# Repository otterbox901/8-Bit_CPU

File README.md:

# 8-Bit CPU

A microcoded 8-bit CPU built from 24 74HC-series logic and memory ICs: custom
instruction set, 4 general-purpose registers, add/subtract ALU with Zero and
Carry flags, and a control unit driven entirely by two EEPROMs.

*Preview from JLCPCB

## Status: In progress

- [x] Instruction set (10 instructions, 1- and 2-byte encodings)
- [x] Microcode ROM generator (`ROM/microcode_rom_gen.py`)
- [x] Emulator + assembler, full test program passing
- [x] Schematic: 24 ICs, 0 ERC errors
- [x] Schematic verified by simulation: the KiCad netlist runs the test program
      at the chip-pin level with the real ROM images (`kicad_files/sim_netlist.py`)
- [x] PCB: 2-layer, 160 × 140 mm, fully routed (Freerouting), GND pour on
      both layers; DRC clean (0 errors, 0 warnings, 0 unconnected) and 0
      schematic-parity differences
- [x] Fabrication outputs: Gerbers + drill (`fab/8-bit-cpu-gerbers.zip`),
      BOM and pick-and-place files
- [ ] Order boards, burn the EEPROMs, and bring up the hardware

## Overview

| | |
|---|---|
| Data path | 8-bit |
| Registers | R0–R3 (2 × 74HC670 register file), plus PC, MAR, IR, A, TEMP |
| Control unit | Microcoded: 2 × 28C256, addressed by opcode, 2-bit step, Z, C |
| ALU | Add, subtract (two's complement), Zero and Carry flags |
| Memory | Harvard: 256 B program EEPROM (28C64), 256 B data SRAM (6116) |
| Clock | 1 MHz canned oscillator (target 1–2 MHz), or external via jumper |
| IC count | 24 (+ oscillator) |
| Board | 2-layer, 160 × 140 mm, SMD logic; EEPROMs and SRAM in DIP sockets so they can be reprogrammed |
| Power | USB-C, 5 V, polyfuse |

## Instruction Set

| Opcode | Mnemonic | Bytes | Operation |
|---|---|---|---|
| `0000` | `NOP` | 1 | No operation |
| `0001` | `LOAD Rd, addr` | 2 | Rd ← RAM[addr] |
| `0010` | `STORE Rd, addr` | 2 | RAM[addr] ← Rd |
| `0011` | `ADD Rd, Rs` | 1 | Rd ← Rd + Rs (sets Z, C) |
| `0100` | `SUB Rd, Rs` | 1 | Rd ← Rd − Rs (sets Z, C; C=1 means no borrow) |
| `0101` | `JMP addr` | 2 | PC ← addr |
| `0110` | `JZ addr` | 2 | PC ← addr if Z |
| `0111` | `JC addr` | 2 | PC ← addr if C |
| `1000` | `MOV Rd, Rs` | 1 | Rd ← Rs |
| `1111` | `HLT` | 1 | Stop the clock |

Unused opcodes behave as `NOP`. Encoding: byte 0 is `[opcode:4][Rd:2][Rs:2]`;
address instructions add one address byte.

Every instruction takes 4 clock cycles (the 2-bit step counter wraps). Step 0
is always the fetch; conditional jumps are resolved by the control ROM, since
Z and C are part of its address.

## Control ROM

`ROM/microcode_rom_gen.py` walks all 256 `(opcode, step, Z, C)` addresses
and writes `microcode_table.csv` (human-readable) and `rom1.bin` / `rom2.bin`
(32 KB images for the two 28C256s). Active-low signals are stored inverted,
so the ROM outputs drive chip enable pins directly without inverter chips.

```bash
cd ROM && python3 microcode_rom_gen.py
```

## Emulator

`emulator.py` runs programs against `microcode_table.csv` directly, and
includes a two-pass assembler (labels, hex/decimal, `.byte`, `.ram addr, val`).

```bash
python3 emulator.py test_program.asm           # full ISA test, 6/6 checks
python3 emulator.py test_program.asm --trace-micro
python3 emulator.py -q test_program.asm        # results only
```

## Schematic

`kicad_files/8-bit cpu.kicad_sch` is **generated**: edit the `PARTS` tables in
`gen_schematic.py` and re-run it. It uses only KiCad's stock symbol and
footprint libraries, except for the 6116 symbol, which is embedded.

```bash
cd kicad_files
python3 gen_schematic.py     # rewrite the schematic
python3 sim_netlist.py       # run test_program.asm on the netlist itself
```

`sim_netlist.py` exports the netlist with `kicad-cli` and models every chip by
its datasheet pin numbers. It fails on bus contention, floating inputs, or
wrong results. Swapped bus bits and a stuck output enable were both confirmed
to be caught.

## PCB

### Ordering the board

Upload `fab/8-bit-cpu-gerbers.zip` to JLCPCB, PCBWay, etc. with:

| Setting | Value |
|---|---|
| Layers | 2 |
| Size | 160 × 140 mm |
| Thickness | 1.6 mm |
| Copper | 1 oz |
| Min track / space | 0.187 mm / 0.2 mm (standard service) |
| Min hole | 0.3 mm (vias 0.6 / 0.3 mm) |
| Plated slots | Yes: 4 on the USB-C shell (0.6 × 1.2 mm) |
| Surface finish | Any (HASL is fine) |

Checked before export: DRC with freshly refilled zones reports 0 errors, 0
warnings, 0 unconnected and 0 schematic-parity issues. The drill file holds
exactly the board's 454 plated holes (329 vias + 125 pads) plus 4 NPTH
mounting holes.

`fab/bom.csv` lists every part to solder. `fab/positions.csv` is the
pick-and-place file (origin at the board's bottom-left corner) for
assembled orders. **Not in the BOM, but needed:**

- 3 × 28-pin 600-mil DIP sockets (U1–U3) and 1 × 24-pin (U4). The
  EEPROMs have to come out to be programmed.
- 1 × 2.54 mm jumper shunt for J2 (pins 1–2 = on-board oscillator).
- The oscillator (Y1) must be a 7050-size, 5 V part with a **tri-state OE**
  on pin 1. HLT stops the clock through that pin.

To regenerate the outputs after a board change:

```bash
P="kicad_files/8-bit cpu.kicad_pcb"
kicad-cli pcb drc --refill-zones --schematic-parity "$P"
kicad-cli pcb export gerbers --layers F.Cu,B.Cu,F.Paste,B.Paste,F.Silkscreen,B.Silkscreen,F.Mask,B.Mask,Edge.Cuts --subtract-soldermask -o fab/gerbers/ "$P"
kicad-cli pcb export drill --format excellon --excellon-separate-th -u mm -o fab/gerbers/ "$P"
kicad-cli pcb export pos --format csv --units mm --side both --use-drill-file-origin -o fab/positions.csv "$P"
kicad-cli sch export bom --fields 'Reference,Value,Footprint,${QUANTITY}' --group-by 'Value,Footprint' -o fab/bom.csv "kicad_files/8-bit cpu.kicad_sch"
```

### Clock and timing

- Registers, PC and flags latch on CLK's **rising** edge.
- The step counter (U7) and a control-ROM address latch (U10, holding the
  opcode and flags) change on CLK's **falling** edge. The control word only
  changes while CLK is low and stays stable, glitch-free, while it's high.
- The two level-sensitive writes, RAM `/WE` and register-file `/Ew`, are
  `NAND(CLK, enable)`, so they only happen during that stable high phase.
- **HLT** drives the oscillator's OE low; the clock stops low (R2 pull-down).
  Reset restarts it.
- **Reset** (SW1, RC + Schmitt '14) asserts immediately but is only
  *released* on a falling clock edge, via U10 bit 6 and two '00 gates.
  Without this, a release while CLK is high skips the first fetch's PC
  increment. The netlist simulation found this bug.
- **J2 CLK SEL**: jumper 1-2 selects the on-board oscillator; 2-3 selects
  `EXT_CLK` for single-stepping from a button or microcontroller. HLT
  can't stop an external clock.
- **J3 DEBUG**: bus, CLK and GND for a logic analyser.

## Known Issues

- **Tracks go down to 0.15 mm** where the router threads between SOIC pins
  (min clearance 0.2 mm); fine for JLCPCB/PCBWay standard service.
- **74HC670 availability**: check stock before ordering; 74LS670 has the same
  pinout (mixing LS into an HC design is fine at these speeds).
- **ERC warnings** (no errors): "symbol doesn't match library" (the embedded
  copies are flattened), tri-state/output on the '245's input side, the
  `local` 6116 symbol, and the intentionally single-pin `EXT_CLK` label.
- No on-board regulator: the board runs straight off USB VBUS.
- Nothing has been tested on real hardware yet.

## Repo Contents

```
├── emulator.py              Microcode-driven emulator + assembler
├── test_program.asm         Full instruction-set test
├── ROM/
│   ├── microcode_rom_gen.py Control ROM generator
│   ├── microcode_table.csv  Human-readable ROM contents
│   └── rom1.bin rom2.bin    28C256 images
├── fab/
│   ├── 8-bit-cpu-gerbers.zip  Upload this to the board house
│   ├── gerbers/               Gerbers + Excellon drill files (+ job file)
│   ├── bom.csv                Bill of materials
│   └── positions.csv          Pick-and-place (board-corner origin)
└── kicad_files/
    ├── sim_netlist.py       Netlist-level simulation
    ├── 8-bit cpu.kicad_sch  Generated schematic
    ├── 8-bit cpu.kicad_pcb  Routed 2-layer board
    └── 8-bit cpu.kicad_pro  Project + design rules
```

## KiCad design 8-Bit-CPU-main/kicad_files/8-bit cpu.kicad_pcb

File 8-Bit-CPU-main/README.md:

# 8-Bit CPU

A microcoded 8-bit CPU built from 24 74HC-series logic and memory ICs: custom
instruction set, 4 general-purpose registers, add/subtract ALU with Zero and
Carry flags, and a control unit driven entirely by two EEPROMs.

This is the **downsized** design. The earlier 50-IC version (16-bit
addresses, AND/OR, a Negative flag, 3 control ROMs, and an AI-generated
schematic that needed many repair passes) is archived in git at commit
`3261fc8`.

## Status: In progress

- [x] Instruction set (10 instructions, 1- and 2-byte encodings)
- [x] Microcode ROM generator (`ROM/microcode_rom_gen.py`)
- [x] Emulator + assembler, full test program passing
- [x] Schematic: 24 ICs, generated from one netlist table
      (`kicad_files/gen_schematic.py`), 0 ERC errors
- [x] Schematic verified by simulation: the KiCad netlist runs the test program
      at the chip-pin level with the real ROM images (`kicad_files/sim_netlist.py`)
- [x] PCB: 2-layer, 160 × 140 mm, fully routed (Freerouting), GND pour on
      both layers; DRC clean (0 errors, 0 warnings, 0 unconnected) and 0
      schematic-parity differences
- [x] Fabrication outputs: Gerbers + drill (`fab/8-bit-cpu-gerbers.zip`),
      BOM and pick-and-place files
- [ ] Order boards, burn the EEPROMs, and bring up the hardware

## Overview

| | |
|---|---|
| Data path | 8-bit |
| Registers | R0–R3 (2 × 74HC670 register file), plus PC, MAR, IR, A, TEMP |
| Control unit | Microcoded: 2 × 28C256, addressed by opcode, 2-bit step, Z, C |
| ALU | Add, subtract (two's complement), Zero and Carry flags |
| Memory | Harvard: 256 B program EEPROM (28C64), 256 B data SRAM (6116) |
| Clock | 1 MHz canned oscillator (target 1–2 MHz), or external via jumper |
| IC count | 24 (+ oscillator) |
| Board | 2-layer, 160 × 140 mm, SMD logic; EEPROMs and SRAM in DIP sockets so they can be reprogrammed |
| Power | USB-C, 5 V, polyfuse |

## Instruction Set

| Opcode | Mnemonic | Bytes | Operation |
|---|---|---|---|
| `0000` | `NOP` | 1 | No operation |
| `0001` | `LOAD Rd, addr` | 2 | Rd ← RAM[addr] |
| `0010` | `STORE Rd, addr` | 2 | RAM[addr] ← Rd |
| `0011` | `ADD Rd, Rs` | 1 | Rd ← Rd + Rs (sets Z, C) |
| `0100` | `SUB Rd, Rs` | 1 | Rd ← Rd − Rs (sets Z, C; C=1 means no borrow) |
| `0101` | `JMP addr` | 2 | PC ← addr |
| `0110` | `JZ addr` | 2 | PC ← addr if Z |
| `0111` | `JC addr` | 2 | PC ← addr if C |
| `1000` | `MOV Rd, Rs` | 1 | Rd ← Rs |
| `1111` | `HLT` | 1 | Stop the clock |

Unused opcodes behave as `NOP`. Encoding: byte 0 is `[opcode:4][Rd:2][Rs:2]`;
address instructions add one address byte.

Every instruction takes 4 clock cycles (the 2-bit step counter wraps). Step 0
is always the fetch; conditional jumps are resolved by the control ROM, since
Z and C are part of its address.

## Control ROM

`ROM/microcode_rom_gen.py` walks all 256 `(opcode, step, Z, C)` addresses
and writes `microcode_table.csv` (human-readable) and `rom1.bin` / `rom2.bin`
(32 KB images for the two 28C256s). Active-low signals are stored inverted,
so the ROM outputs drive chip enable pins directly without inverter chips.

```bash
cd ROM && python3 microcode_rom_gen.py
```

## Emulator

`emulator.py` runs programs against `microcode_table.csv` directly, and
includes a two-pass assembler (labels, hex/decimal, `.byte`, `.ram addr, val`).

```bash
python3 emulator.py test_program.asm           # full ISA test, 6/6 checks
python3 emulator.py test_program.asm --trace-micro
python3 emulator.py -q test_program.asm        # results only
```

## Schematic

`kicad_files/8-bit cpu.kicad_sch` is **generated**: edit the `PARTS` tables in
`gen_schematic.py` and re-run it. It uses only KiCad's stock symbol and
footprint libraries, except for the 6116 symbol, which is embedded.

```bash
cd kicad_files
python3 gen_schematic.py     # rewrite the schematic
python3 sim_netlist.py       # run test_program.asm on the netlist itself
```

`sim_netlist.py` exports the netlist with `kicad-cli` and models every chip by
its datasheet pin numbers. It fails on bus contention, floating inputs, or
wrong results. Swapped bus bits and a stuck output enable were both confirmed
to be caught.

## PCB

`kicad_files/gen_pcb.py` builds the board from the schematic's netlist:

```bash
cd kicad_files
python3 gen_pcb.py place                          # new, unrouted board
python3 gen_pcb.py route --freerouting <path>     # autoroute + GND pours
python3 gen_pcb.py pour                           # redo pours only (keeps routing)
kicad-cli pcb drc --schematic-parity "8-bit cpu.kicad_pcb"
```

`place` overwrites any routing, so after hand-editing the board, use KiCad's
*Update PCB from Schematic* instead. Footprints are linked to their symbols,
and the schematic's symbol IDs stay the same when it's regenerated.
Placement lives in the `PLACEMENT` table. Each 100 nF cap sits right above
its IC's VCC pin. Power nets (+5V, GND, VBUS) use a 0.6 mm `Power` net class.

### Ordering the board

Upload `fab/8-bit-cpu-gerbers.zip` to JLCPCB, PCBWay, etc. with:

| Setting | Value |
|---|---|
| Layers | 2 |
| Size | 160 × 140 mm |
| Thickness | 1.6 mm |
| Copper | 1 oz |
| Min track / space | 0.187 mm / 0.2 mm (standard service) |
| Min hole | 0.3 mm (vias 0.6 / 0.3 mm) |
| Plated slots | Yes: 4 on the USB-C shell (0.6 × 1.2 mm) |
| Surface finish | Any (HASL is fine) |

Checked before export: DRC with freshly refilled zones reports 0 errors, 0
warnings, 0 unconnected and 0 schematic-parity issues. The drill file holds
exactly the board's 454 plated holes (329 vias + 125 pads) plus 4 NPTH
mounting holes.

`fab/bom.csv` lists every part to solder. `fab/positions.csv` is the
pick-and-place file (origin at the board's bottom-left corner) for
assembled orders. **Not in the BOM, but needed:**

- 3 × 28-pin 600-mil DIP sockets (U1–U3) and 1 × 24-pin (U4). The
  EEPROMs have to come out to be programmed.
- 1 × 2.54 mm jumper shunt for J2 (pins 1–2 = on-board oscillator).
- The oscillator (Y1) must be a 7050-size, 5 V part with a **tri-state OE**
  on pin 1. HLT stops the clock through that pin.

To regenerate the outputs after a board change:

```bash
P="kicad_files/8-bit cpu.kicad_pcb"
kicad-cli pcb drc --refill-zones --schematic-parity "$P"
kicad-cli pcb export gerbers --layers F.Cu,B.Cu,F.Paste,B.Paste,F.Silkscreen,B.Silkscreen,F.Mask,B.Mask,Edge.Cuts --subtract-soldermask -o fab/gerbers/ "$P"
kicad-cli pcb export drill --format excellon --excellon-separate-th -u mm -o fab/gerbers/ "$P"
kicad-cli pcb export pos --format csv --units mm --side both --use-drill-file-origin -o fab/positions.csv "$P"
kicad-cli sch export bom --fields 'Reference,Value,Footprint,${QUANTITY}' --group-by 'Value,Footprint' -o fab/bom.csv "kicad_files/8-bit cpu.kicad_sch"
```

### Clock and timing

- Registers, PC and flags latch on CLK's **rising** edge.
- The step counter (U7) and a control-ROM address latch (U10, holding the
  opcode and flags) change on CLK's **falling** edge. The control word only
  changes while CLK is low and stays stable, glitch-free, while it's high.
- The two level-sensitive writes, RAM `/WE` and register-file `/Ew`, are
  `NAND(CLK, enable)`, so they only happen during that stable high phase.
- **HLT** drives the oscillator's OE low; the clock stops low (R2 pull-down).
  Reset restarts it.
- **Reset** (SW1, RC + Schmitt '14) asserts immediately but is only
  *released* on a falling clock edge, via U10 bit 6 and two '00 gates.
  Without this, a release while CLK is high skips the first fetch's PC
  increment. The netlist simulation found this bug.
- **J2 CLK SEL**: jumper 1-2 selects the on-board oscillator; 2-3 selects
  `EXT_CLK` for single-stepping from a button or microcontroller. HLT
  can't stop an external clock.
- **J3 DEBUG**: bus, CLK and GND for a logic analyser.

## Known Issues

- **Tracks go down to 0.15 mm** where the router threads between SOIC pins
  (min clearance 0.2 mm); fine for JLCPCB/PCBWay standard service.
- **74HC670 availability**: check stock before ordering; 74LS670 has the same
  pinout (mixing LS into an HC design is fine at these speeds).
- **ERC warnings** (no errors): "symbol doesn't match library" (the embedded
  copies are flattened), tri-state/output on the '245's input side, the
  `local` 6116 symbol, and the intentionally single-pin `EXT_CLK` label.
- No on-board regulator: the board runs straight off USB VBUS.
- Nothing has been tested on real hardware yet.

## Repo Contents

```
├── emulator.py              Microcode-driven emulator + assembler
├── test_program.asm         Full instruction-set test
├── ROM/
│   ├── microcode_rom_gen.py Control ROM generator
│   ├── microcode_table.csv  Human-readable ROM contents
│   └── rom1.bin rom2.bin    28C256 images
├── fab/
│   ├── 8-bit-cpu-gerbers.zip  Upload this to the board house
│   ├── gerbers/               Gerbers + Excellon drill files (+ job file)
│   ├── bom.csv                Bill of materials
│   └── positions.csv          Pick-and-place (board-corner origin)
└── kicad_files/
    ├── gen_schematic.py     Schematic generator (the design source)
    ├── sim_netlist.py       Netlist-level simulation
    ├── gen_pcb.py           Board generator: placement, routing, pours
    ├── 8-bit cpu.kicad_sch  Generated schematic
    ├── 8-bit cpu.kicad_pcb  Routed 2-layer board
    └── 8-bit cpu.kicad_pro  Project + design rules (written by gen_pcb.py)
```

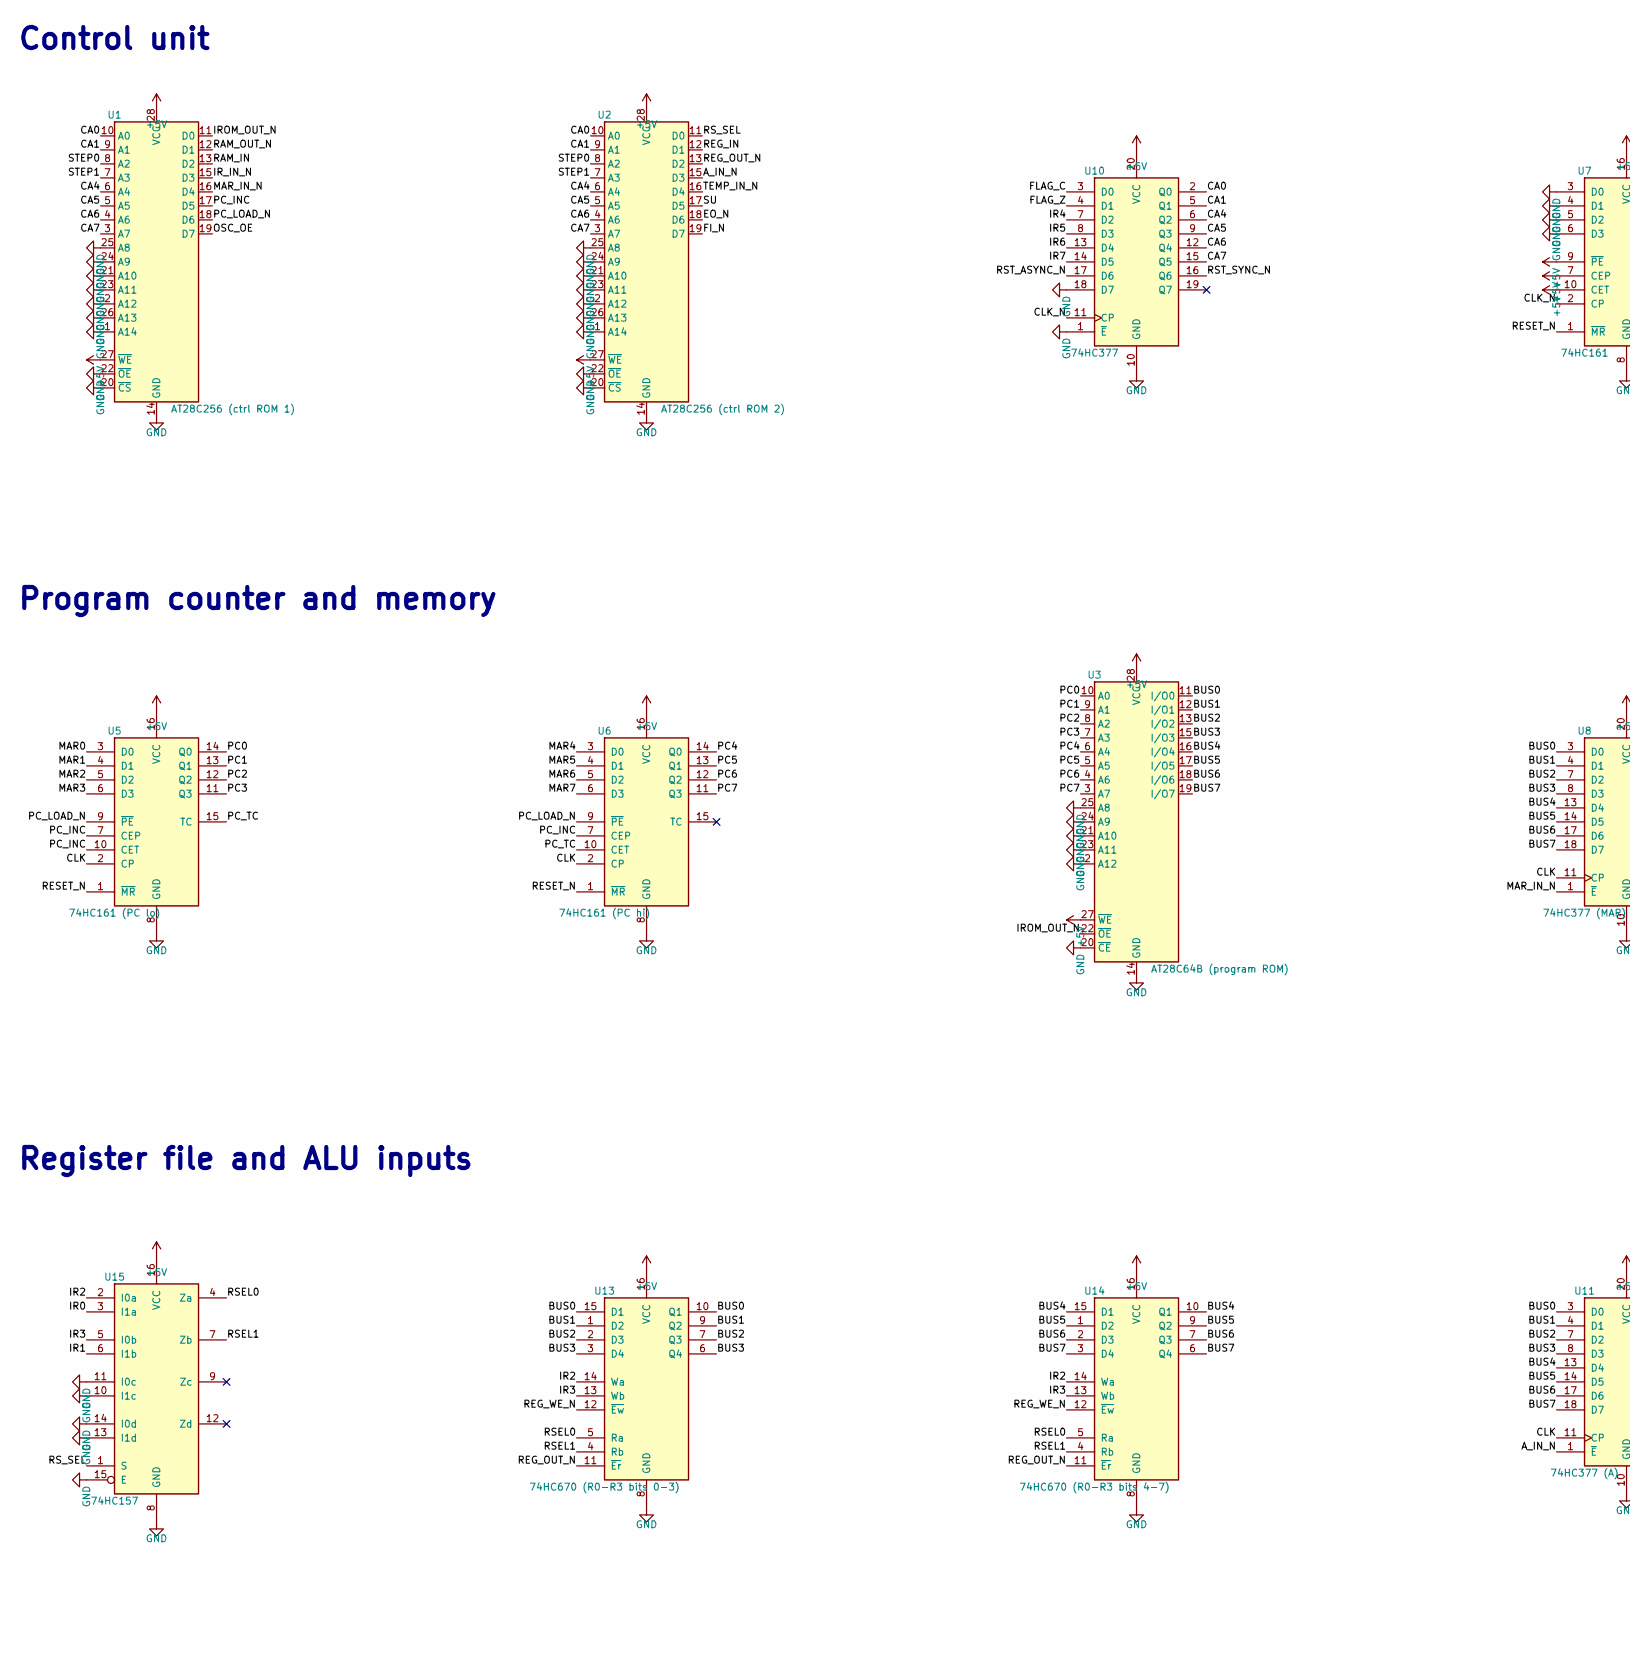
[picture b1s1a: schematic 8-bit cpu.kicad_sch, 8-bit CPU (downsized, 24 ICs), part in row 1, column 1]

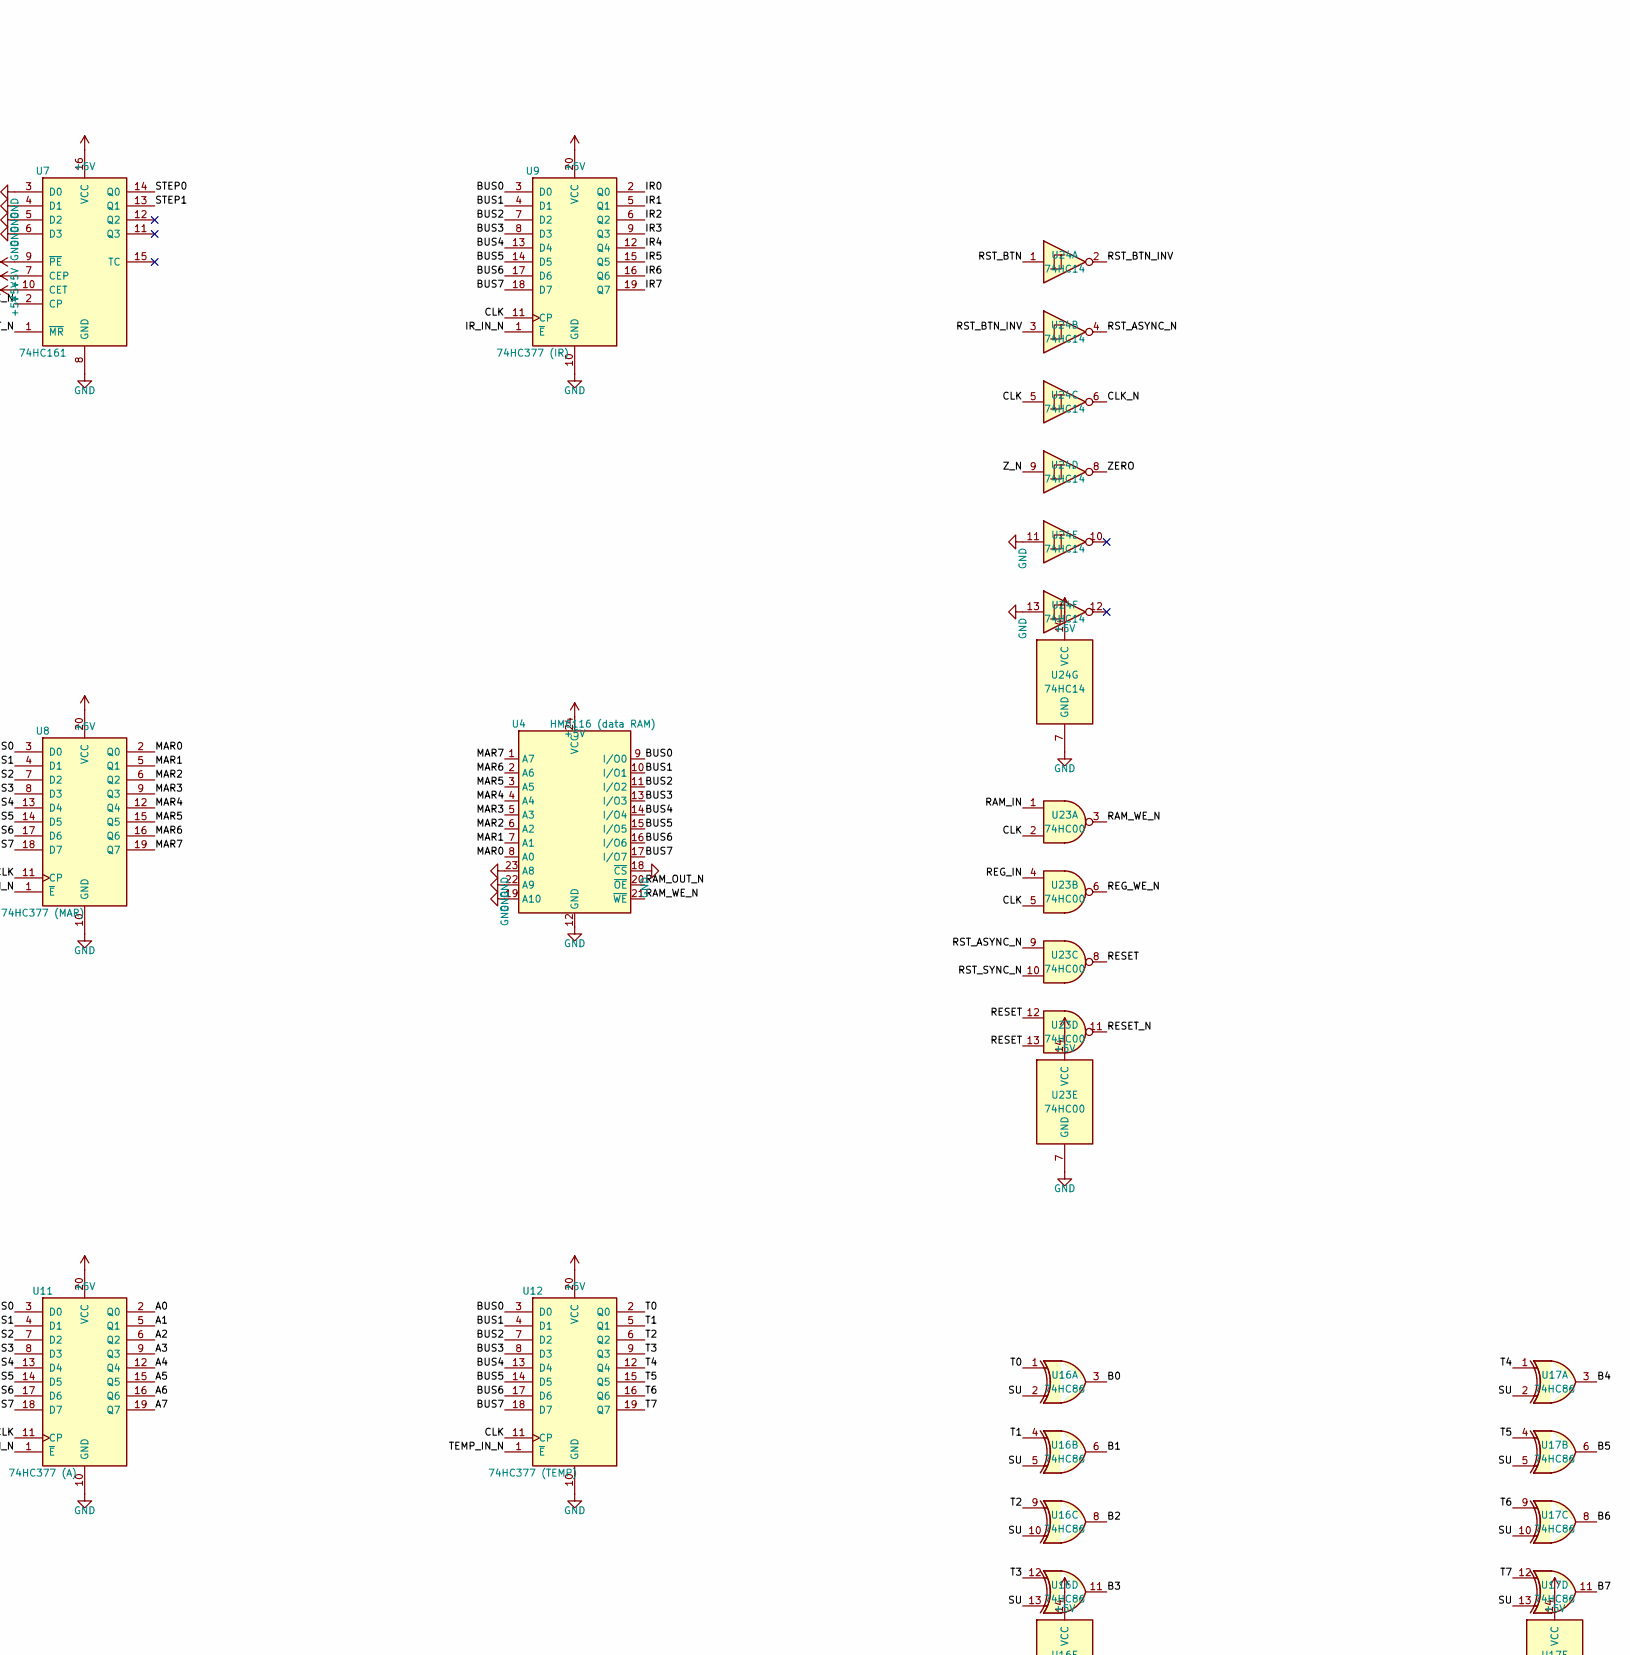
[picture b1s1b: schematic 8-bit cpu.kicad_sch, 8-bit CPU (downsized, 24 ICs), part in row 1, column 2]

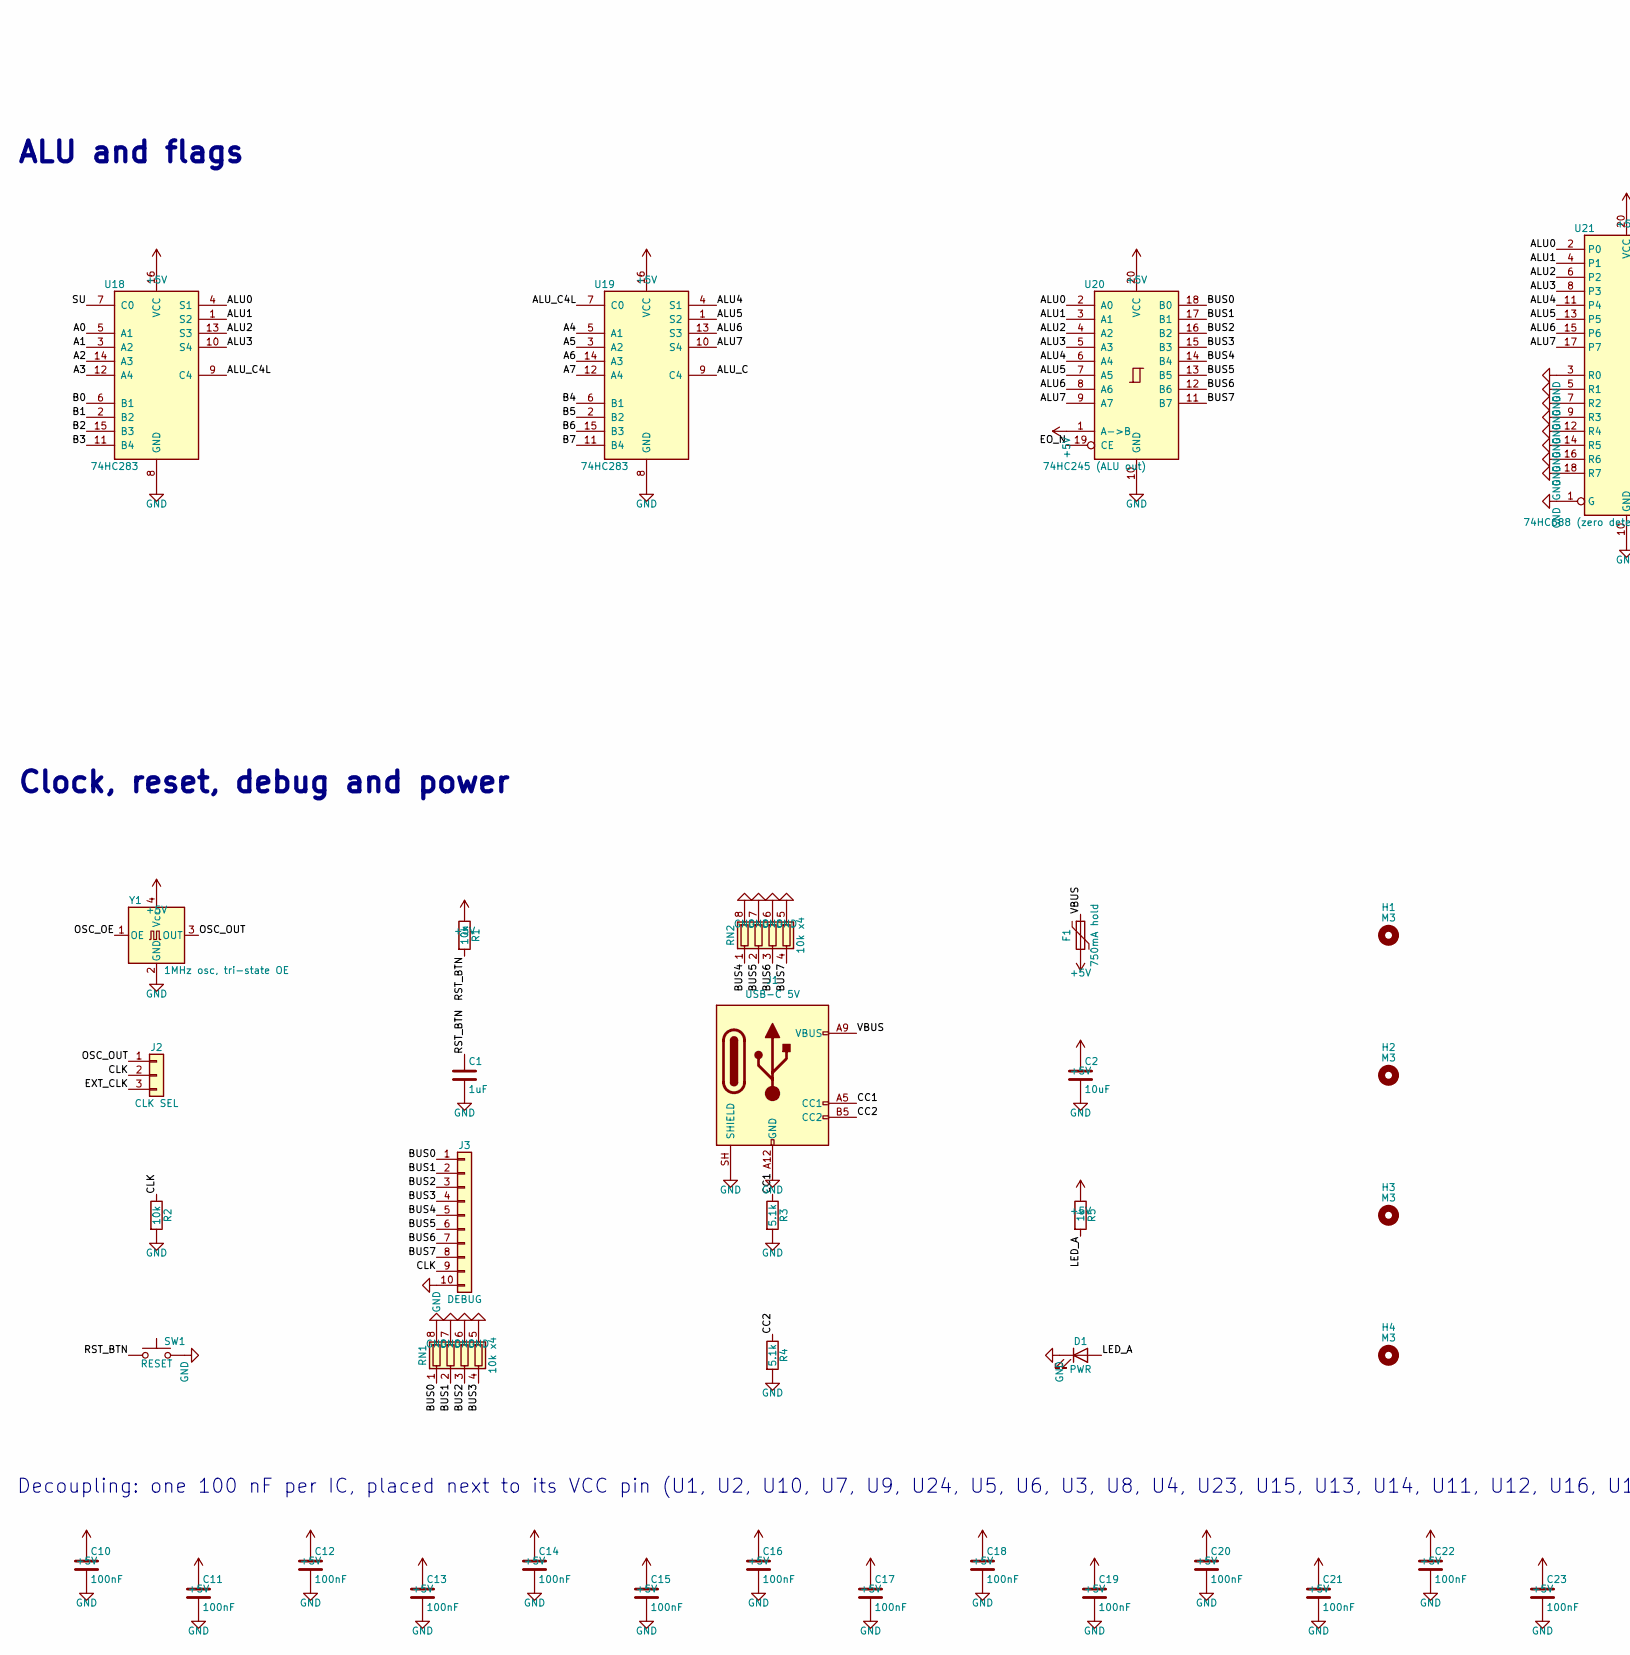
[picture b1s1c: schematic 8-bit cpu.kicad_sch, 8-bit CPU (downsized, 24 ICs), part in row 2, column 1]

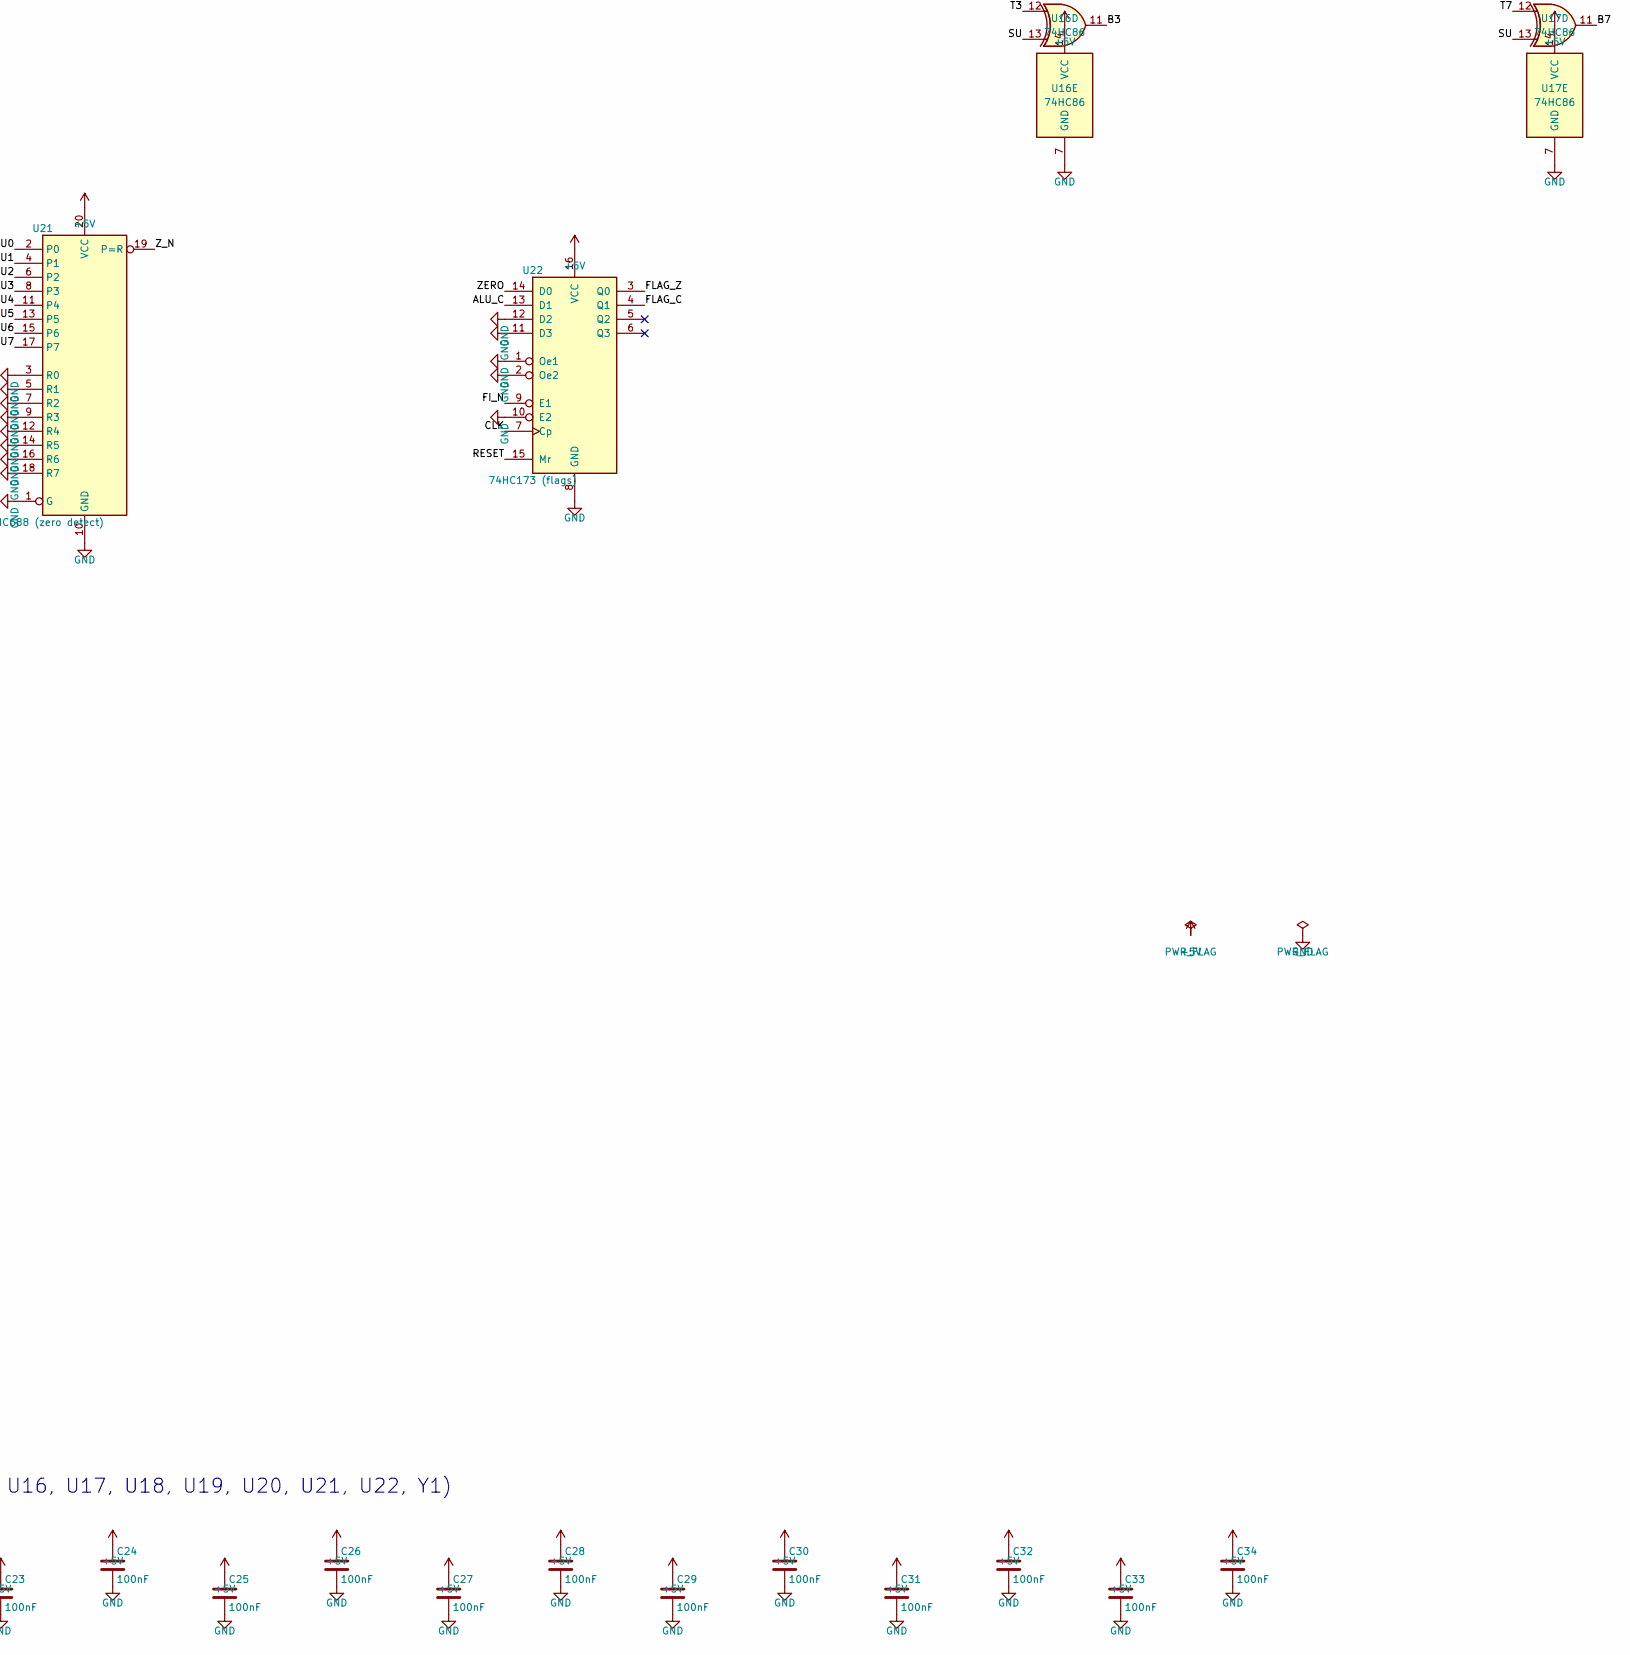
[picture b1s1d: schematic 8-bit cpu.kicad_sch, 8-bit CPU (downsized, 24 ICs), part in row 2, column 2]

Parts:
C1: 1uF; C_0603_1608Metric
C2: 10uF; C_0805_2012Metric
C10, C11, C12, C13, C14, C15, C16, C17, C18, C19, C20, C21, C22, C23, C24, C25, C26, C27, C28, C29, C30, C31, C32, C33, C34: 100nF; C_0603_1608Metric
D1: PWR; LED_0603_1608Metric
F1: 750mA hold; Fuse_1206_3216Metric
H1, H2, H3, H4: M3; MountingHole_3.2mm_M3
J1: USB-C 5V; USB_C_Receptacle_GCT_USB4125-xx-x_6P_TopMnt_Horizontal
J2: CLK SEL; PinHeader_1x03_P2.54mm_Vertical
J3: DEBUG; PinHeader_1x10_P2.54mm_Vertical
R1, R2: 10k; R_0603_1608Metric
R3, R4: 5.1k; R_0603_1608Metric
R5: 1k; R_0603_1608Metric
RN1, RN2: 10k x4; R_Array_Convex_4x0603
SW1: RESET; SW_SPST_TL3342
U1: AT28C256 (ctrl ROM 1); DIP-28_W15.24mm_Socket
U2: AT28C256 (ctrl ROM 2); DIP-28_W15.24mm_Socket
U3: AT28C64B (program ROM); DIP-28_W15.24mm_Socket
U4: HM6116 (data RAM); DIP-24_W15.24mm_Socket
U5: 74HC161 (PC lo); SOIC-16_3.9x9.9mm_P1.27mm
U6: 74HC161 (PC hi); SOIC-16_3.9x9.9mm_P1.27mm
U7: 74HC161; SOIC-16_3.9x9.9mm_P1.27mm
U8: 74HC377 (MAR); SOIC-20W_7.5x12.8mm_P1.27mm
U9: 74HC377 (IR); SOIC-20W_7.5x12.8mm_P1.27mm
U10: 74HC377; SOIC-20W_7.5x12.8mm_P1.27mm
U11: 74HC377 (A); SOIC-20W_7.5x12.8mm_P1.27mm
U12: 74HC377 (TEMP); SOIC-20W_7.5x12.8mm_P1.27mm
U13: 74HC670 (R0-R3 bits 0-3); SOIC-16_3.9x9.9mm_P1.27mm
U14: 74HC670 (R0-R3 bits 4-7); SOIC-16_3.9x9.9mm_P1.27mm
U15: 74HC157; SOIC-16_3.9x9.9mm_P1.27mm
U16, U17: 74HC86; SOIC-14_3.9x8.7mm_P1.27mm
U18, U19: 74HC283; SOIC-16_3.9x9.9mm_P1.27mm
U20: 74HC245 (ALU out); SOIC-20W_7.5x12.8mm_P1.27mm
U21: 74HC688 (zero detect); SOIC-20W_7.5x12.8mm_P1.27mm
U22: 74HC173 (flags); SOIC-16_3.9x9.9mm_P1.27mm
U23: 74HC00; SOIC-14_3.9x8.7mm_P1.27mm
U24: 74HC14; SOIC-14_3.9x8.7mm_P1.27mm
Y1: 1MHz osc, tri-state OE; Oscillator_SMD_SeikoEpson_SG8002CA-4Pin_7.0x5.0mm

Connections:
+5V: C2.1, C10.1, C11.1, C12.1, C13.1, C14.1, C15.1, C16.1, C17.1, C18.1, C19.1, C20.1, C21.1, C22.1, C23.1, C24.1, C25.1, C26.1, C27.1, C28.1, C29.1, C30.1, C31.1, C32.1, C33.1, C34.1, F1.2, R1.1, R5.1, U1.27 (~WE), U1.28 (VCC), U2.27 (~WE), U2.28 (VCC), U3.27 (~WE), U3.28 (VCC), U4.24 (VCC), U5.16 (VCC), U6.16 (VCC), U7.7 (CEP), U7.9 (~PE), U7.10 (CET), U7.16 (VCC), U8.20 (VCC), U9.20 (VCC), U10.20 (VCC), U11.20 (VCC), U12.20 (VCC), U13.16 (VCC), U14.16 (VCC), U15.16 (VCC), U16.14 (VCC), U17.14 (VCC), U18.16 (VCC), U19.16 (VCC), U20.1 (A->B), U20.20 (VCC), U21.20 (VCC), U22.16 (VCC), U23.14 (VCC), U24.14 (VCC), Y1.4 (Vcc)
/A0: U11.2 (Q0), U18.5 (A1)
/A1: U11.5 (Q1), U18.3 (A2)
/A2: U11.6 (Q2), U18.14 (A3)
/A3: U11.9 (Q3), U18.12 (A4)
/A4: U11.12 (Q4), U19.5 (A1)
/A5: U11.15 (Q5), U19.3 (A2)
/A6: U11.16 (Q6), U19.14 (A3)
/A7: U11.19 (Q7), U19.12 (A4)
/ALU0: U18.4 (S1), U20.2 (A0), U21.2 (P0)
/ALU1: U18.1 (S2), U20.3 (A1), U21.4 (P1)
/ALU2: U18.13 (S3), U20.4 (A2), U21.6 (P2)
/ALU3: U18.10 (S4), U20.5 (A3), U21.8 (P3)
/ALU4: U19.4 (S1), U20.6 (A4), U21.11 (P4)
/ALU5: U19.1 (S2), U20.7 (A5), U21.13 (P5)
/ALU6: U19.13 (S3), U20.8 (A6), U21.15 (P6)
/ALU7: U19.10 (S4), U20.9 (A7), U21.17 (P7)
/ALU_C: U19.9 (C4), U22.13 (D1)
/ALU_C4L: U18.9 (C4), U19.7 (C0)
/A_IN_N: U2.15 (D3), U11.1 (~E)
/B0: U16.3, U18.6 (B1)
/B1: U16.6, U18.2 (B2)
/B2: U16.8, U18.15 (B3)
/B3: U16.11, U18.11 (B4)
/B4: U17.3, U19.6 (B1)
/B5: U17.6, U19.2 (B2)
/B6: U17.8, U19.15 (B3)
/B7: U17.11, U19.11 (B4)
/BUS0: J3.1, RN1.1 (R1.1), U3.11 (I/O0), U4.9 (I/O0), U8.3 (D0), U9.3 (D0), U11.3 (D0), U12.3 (D0), U13.10 (Q1), U13.15 (D1), U20.18 (B0)
/BUS1: J3.2, RN1.2 (R2.1), U3.12 (I/O1), U4.10 (I/O1), U8.4 (D1), U9.4 (D1), U11.4 (D1), U12.4 (D1), U13.1 (D2), U13.9 (Q2), U20.17 (B1)
/BUS2: J3.3, RN1.3 (R3.1), U3.13 (I/O2), U4.11 (I/O2), U8.7 (D2), U9.7 (D2), U11.7 (D2), U12.7 (D2), U13.2 (D3), U13.7 (Q3), U20.16 (B2)
/BUS3: J3.4, RN1.4 (R4.1), U3.15 (I/O3), U4.13 (I/O3), U8.8 (D3), U9.8 (D3), U11.8 (D3), U12.8 (D3), U13.3 (D4), U13.6 (Q4), U20.15 (B3)
/BUS4: J3.5, RN2.1 (R1.1), U3.16 (I/O4), U4.14 (I/O4), U8.13 (D4), U9.13 (D4), U11.13 (D4), U12.13 (D4), U14.10 (Q1), U14.15 (D1), U20.14 (B4)
/BUS5: J3.6, RN2.2 (R2.1), U3.17 (I/O5), U4.15 (I/O5), U8.14 (D5), U9.14 (D5), U11.14 (D5), U12.14 (D5), U14.1 (D2), U14.9 (Q2), U20.13 (B5)
/BUS6: J3.7, RN2.3 (R3.1), U3.18 (I/O6), U4.16 (I/O6), U8.17 (D6), U9.17 (D6), U11.17 (D6), U12.17 (D6), U14.2 (D3), U14.7 (Q3), U20.12 (B6)
/BUS7: J3.8, RN2.4 (R4.1), U3.19 (I/O7), U4.17 (I/O7), U8.18 (D7), U9.18 (D7), U11.18 (D7), U12.18 (D7), U14.3 (D4), U14.6 (Q4), U20.11 (B7)
/CA0: U1.10 (A0), U2.10 (A0), U10.2 (Q0)
/CA1: U1.9 (A1), U2.9 (A1), U10.5 (Q1)
/CA4: U1.6 (A4), U2.6 (A4), U10.6 (Q2)
/CA5: U1.5 (A5), U2.5 (A5), U10.9 (Q3)
/CA6: U1.4 (A6), U2.4 (A6), U10.12 (Q4)
/CA7: U1.3 (A7), U2.3 (A7), U10.15 (Q5)
/CC1: J1.A5 (CC1), R3.1
/CC2: J1.B5 (CC2), R4.1
/CLK: J2.2, J3.9, R2.1, U5.2 (CP), U6.2 (CP), U8.11 (CP), U9.11 (CP), U11.11 (CP), U12.11 (CP), U22.7 (Cp), U23.2, U23.5, U24.5
/CLK_N: U7.2 (CP), U10.11 (CP), U24.6
/EO_N: U2.18 (D6), U20.19 (CE)
/EXT_CLK: J2.3
/FI_N: U2.19 (D7), U22.9 (E1)
/FLAG_C: U10.3 (D0), U22.4 (Q1)
/FLAG_Z: U10.4 (D1), U22.3 (Q0)
/IR0: U9.2 (Q0), U15.3 (I1a)
/IR1: U9.5 (Q1), U15.6 (I1b)
/IR2: U9.6 (Q2), U13.14 (Wa), U14.14 (Wa), U15.2 (I0a)
/IR3: U9.9 (Q3), U13.13 (Wb), U14.13 (Wb), U15.5 (I0b)
/IR4: U9.12 (Q4), U10.7 (D2)
/IR5: U9.15 (Q5), U10.8 (D3)
/IR6: U9.16 (Q6), U10.13 (D4)
/IR7: U9.19 (Q7), U10.14 (D5)
/IROM_OUT_N: U1.11 (D0), U3.22 (~OE)
/IR_IN_N: U1.15 (D3), U9.1 (~E)
/LED_A: D1.2 (A), R5.2
/MAR0: U4.8 (A0), U5.3 (D0), U8.2 (Q0)
/MAR1: U4.7 (A1), U5.4 (D1), U8.5 (Q1)
/MAR2: U4.6 (A2), U5.5 (D2), U8.6 (Q2)
/MAR3: U4.5 (A3), U5.6 (D3), U8.9 (Q3)
/MAR4: U4.4 (A4), U6.3 (D0), U8.12 (Q4)
/MAR5: U4.3 (A5), U6.4 (D1), U8.15 (Q5)
/MAR6: U4.2 (A6), U6.5 (D2), U8.16 (Q6)
/MAR7: U4.1 (A7), U6.6 (D3), U8.19 (Q7)
/MAR_IN_N: U1.16 (D4), U8.1 (~E)
/OSC_OE: U1.19 (D7), Y1.1 (OE)
/OSC_OUT: J2.1, Y1.3 (OUT)
/PC0: U3.10 (A0), U5.14 (Q0)
/PC1: U3.9 (A1), U5.13 (Q1)
/PC2: U3.8 (A2), U5.12 (Q2)
/PC3: U3.7 (A3), U5.11 (Q3)
/PC4: U3.6 (A4), U6.14 (Q0)
/PC5: U3.5 (A5), U6.13 (Q1)
/PC6: U3.4 (A6), U6.12 (Q2)
/PC7: U3.3 (A7), U6.11 (Q3)
/PC_INC: U1.17 (D5), U5.7 (CEP), U5.10 (CET), U6.7 (CEP)
/PC_LOAD_N: U1.18 (D6), U5.9 (~PE), U6.9 (~PE)
/PC_TC: U5.15 (TC), U6.10 (CET)
/RAM_IN: U1.13 (D2), U23.1
/RAM_OUT_N: U1.12 (D1), U4.20 (~OE)
/RAM_WE_N: U4.21 (~WE), U23.3
/REG_IN: U2.12 (D1), U23.4
/REG_OUT_N: U2.13 (D2), U13.11 (~Er), U14.11 (~Er)
/REG_WE_N: U13.12 (~Ew), U14.12 (~Ew), U23.6
/RESET: U22.15 (Mr), U23.8, U23.12, U23.13
/RESET_N: U5.1 (~MR), U6.1 (~MR), U7.1 (~MR), U23.11
/RSEL0: U13.5 (Ra), U14.5 (Ra), U15.4 (Za)
/RSEL1: U13.4 (Rb), U14.4 (Rb), U15.7 (Zb)
/RST_ASYNC_N: U10.17 (D6), U23.9, U24.4
/RST_BTN: C1.1, R1.2, SW1.1, U24.1
/RST_BTN_INV: U24.2, U24.3
/RST_SYNC_N: U10.16 (Q6), U23.10
/RS_SEL: U2.11 (D0), U15.1 (S)
/STEP0: U1.8 (A2), U2.8 (A2), U7.14 (Q0)
/STEP1: U1.7 (A3), U2.7 (A3), U7.13 (Q1)
/SU: U2.17 (D5), U16.2, U16.5, U16.10, U16.13, U17.2, U17.5, U17.10, U17.13, U18.7 (C0)
/T0: U12.2 (Q0), U16.1
/T1: U12.5 (Q1), U16.4
/T2: U12.6 (Q2), U16.9
/T3: U12.9 (Q3), U16.12
/T4: U12.12 (Q4), U17.1
/T5: U12.15 (Q5), U17.4
/T6: U12.16 (Q6), U17.9
/T7: U12.19 (Q7), U17.12
/TEMP_IN_N: U2.16 (D4), U12.1 (~E)
/VBUS: F1.1, J1.A9 (VBUS), J1.B9 (VBUS)
/ZERO: U22.14 (D0), U24.8
/Z_N: U21.19 (P=R), U24.9
GND: C1.2, C2.2, C10.2, C11.2, C12.2, C13.2, C14.2, C15.2, C16.2, C17.2, C18.2, C19.2, C20.2, C21.2, C22.2, C23.2, C24.2, C25.2, C26.2, C27.2, C28.2, C29.2, C30.2, C31.2, C32.2, C33.2, C34.2, D1.1 (K), J1.A12 (GND), J1.B12 (GND), J1.SH (SHIELD), J3.10, R2.2, R3.2, R4.2, RN1.5 (R4.2), RN1.6 (R3.2), RN1.7 (R2.2), RN1.8 (R1.2), RN2.5 (R4.2), RN2.6 (R3.2), RN2.7 (R2.2), RN2.8 (R1.2), SW1.2, U1.1 (A14), U1.2 (A12), U1.14 (GND), U1.20 (~CS), U1.21 (A10), U1.22 (~OE), U1.23 (A11), U1.24 (A9), U1.25 (A8), U1.26 (A13), U2.1 (A14), U2.2 (A12), U2.14 (GND), U2.20 (~CS), U2.21 (A10), U2.22 (~OE), U2.23 (A11), U2.24 (A9), U2.25 (A8), U2.26 (A13), U3.2 (A12), U3.14 (GND), U3.20 (~CE), U3.21 (A10), U3.23 (A11), U3.24 (A9), U3.25 (A8), U4.12 (GND), U4.18 (~CS), U4.19 (A10), U4.22 (A9), U4.23 (A8), U5.8 (GND), U6.8 (GND), U7.3 (D0), U7.4 (D1), U7.5 (D2), U7.6 (D3), U7.8 (GND), U8.10 (GND), U9.10 (GND), U10.1 (~E), U10.10 (GND), U10.18 (D7), U11.10 (GND), U12.10 (GND), U13.8 (GND), U14.8 (GND), U15.8 (GND), U15.10 (I1c), U15.11 (I0c), U15.13 (I1d), U15.14 (I0d), U15.15 (E), U16.7 (GND), U17.7 (GND), U18.8 (GND), U19.8 (GND), U20.10 (GND), U21.1 (G), U21.3 (R0), U21.5 (R1), U21.7 (R2), U21.9 (R3), U21.10 (GND), U21.12 (R4), U21.14 (R5), U21.16 (R6), U21.18 (R7), U22.1 (Oe1), U22.2 (Oe2), U22.8 (GND), U22.10 (E2), U22.11 (D3), U22.12 (D2), U23.7 (GND), U24.7 (GND), U24.11, U24.13, Y1.2 (GND)

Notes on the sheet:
Control unit
Program counter and memory
Register file and ALU inputs
ALU and flags
Clock, reset, debug and power
Decoupling: one 100 nF per IC, placed next to its VCC pin (U1, U2, U10, U7, U9, U24, U5, U6, U3, U8, U4, U23, U15, U13, U14, U11, U12, U16, U17, U18, U19, U20, U21, U22, Y1)
